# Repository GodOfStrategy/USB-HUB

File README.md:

# USB-HUB
USB-C PD USB 3.0 Hub

A compact USB 3.0 hub based on the TUSB8041 hub controller with USB-C Power Delivery, SD/microSD support, and per-port power protection.
I made this porject to make use of the empty USB-C 3.0 port on my laptop, and since my laptop does not have a SD reader, this hub would be useful.
Features
2× USB 3.0 Type-A ports
SD card reader
microSD card reader
USB-C upstream connection
USB Power Delivery (UPD350A)
USB-C orientation detection and lane switching
Per-port overcurrent protection
USB 3.0 SuperSpeed (5 Gbps)
# Architecture:
USB-C
│
UPD350A (PD Controller)
│
HD3SS3212 (USB-C Lane Mux)
│
TUSB8041 (USB 3.0 Hub)
├── USB 3.0 Port #1
├── USB 3.0 Port #2
├── GL823K SD Reader
└── GL823K microSD Reader

# Power System:
USB-C PD input (5–20V)
Buck converter → 5V rail
Buck converter → 3.3V rail
Buck converter → 1.8V rail
LDO → 1.1V rail (TUSB8041 core)
Protection
TPS2553 on each downstream USB port
900 mA current limit per port
Overcurrent fault reporting to TUSB8041

# Key Components:
Component	PurposeTUSB8041	USB 3.0 Hub Controller
UPD350A	USB-C PD & Orientation Detection
HD3SS3212	SuperSpeed Lane Multiplexer
TPS2553	Port Power Protection
GL823K	USB-to-SD Bridge

# Design Notes:
USB 3.0 differential pairs routed at 90 Ω differential impedance.
HD3SS3212 SEL pin driven by UPD350A orientation output.
TUSB8041 configured for individual port power control.
External 24 MHz crystal used for hub clock generation.

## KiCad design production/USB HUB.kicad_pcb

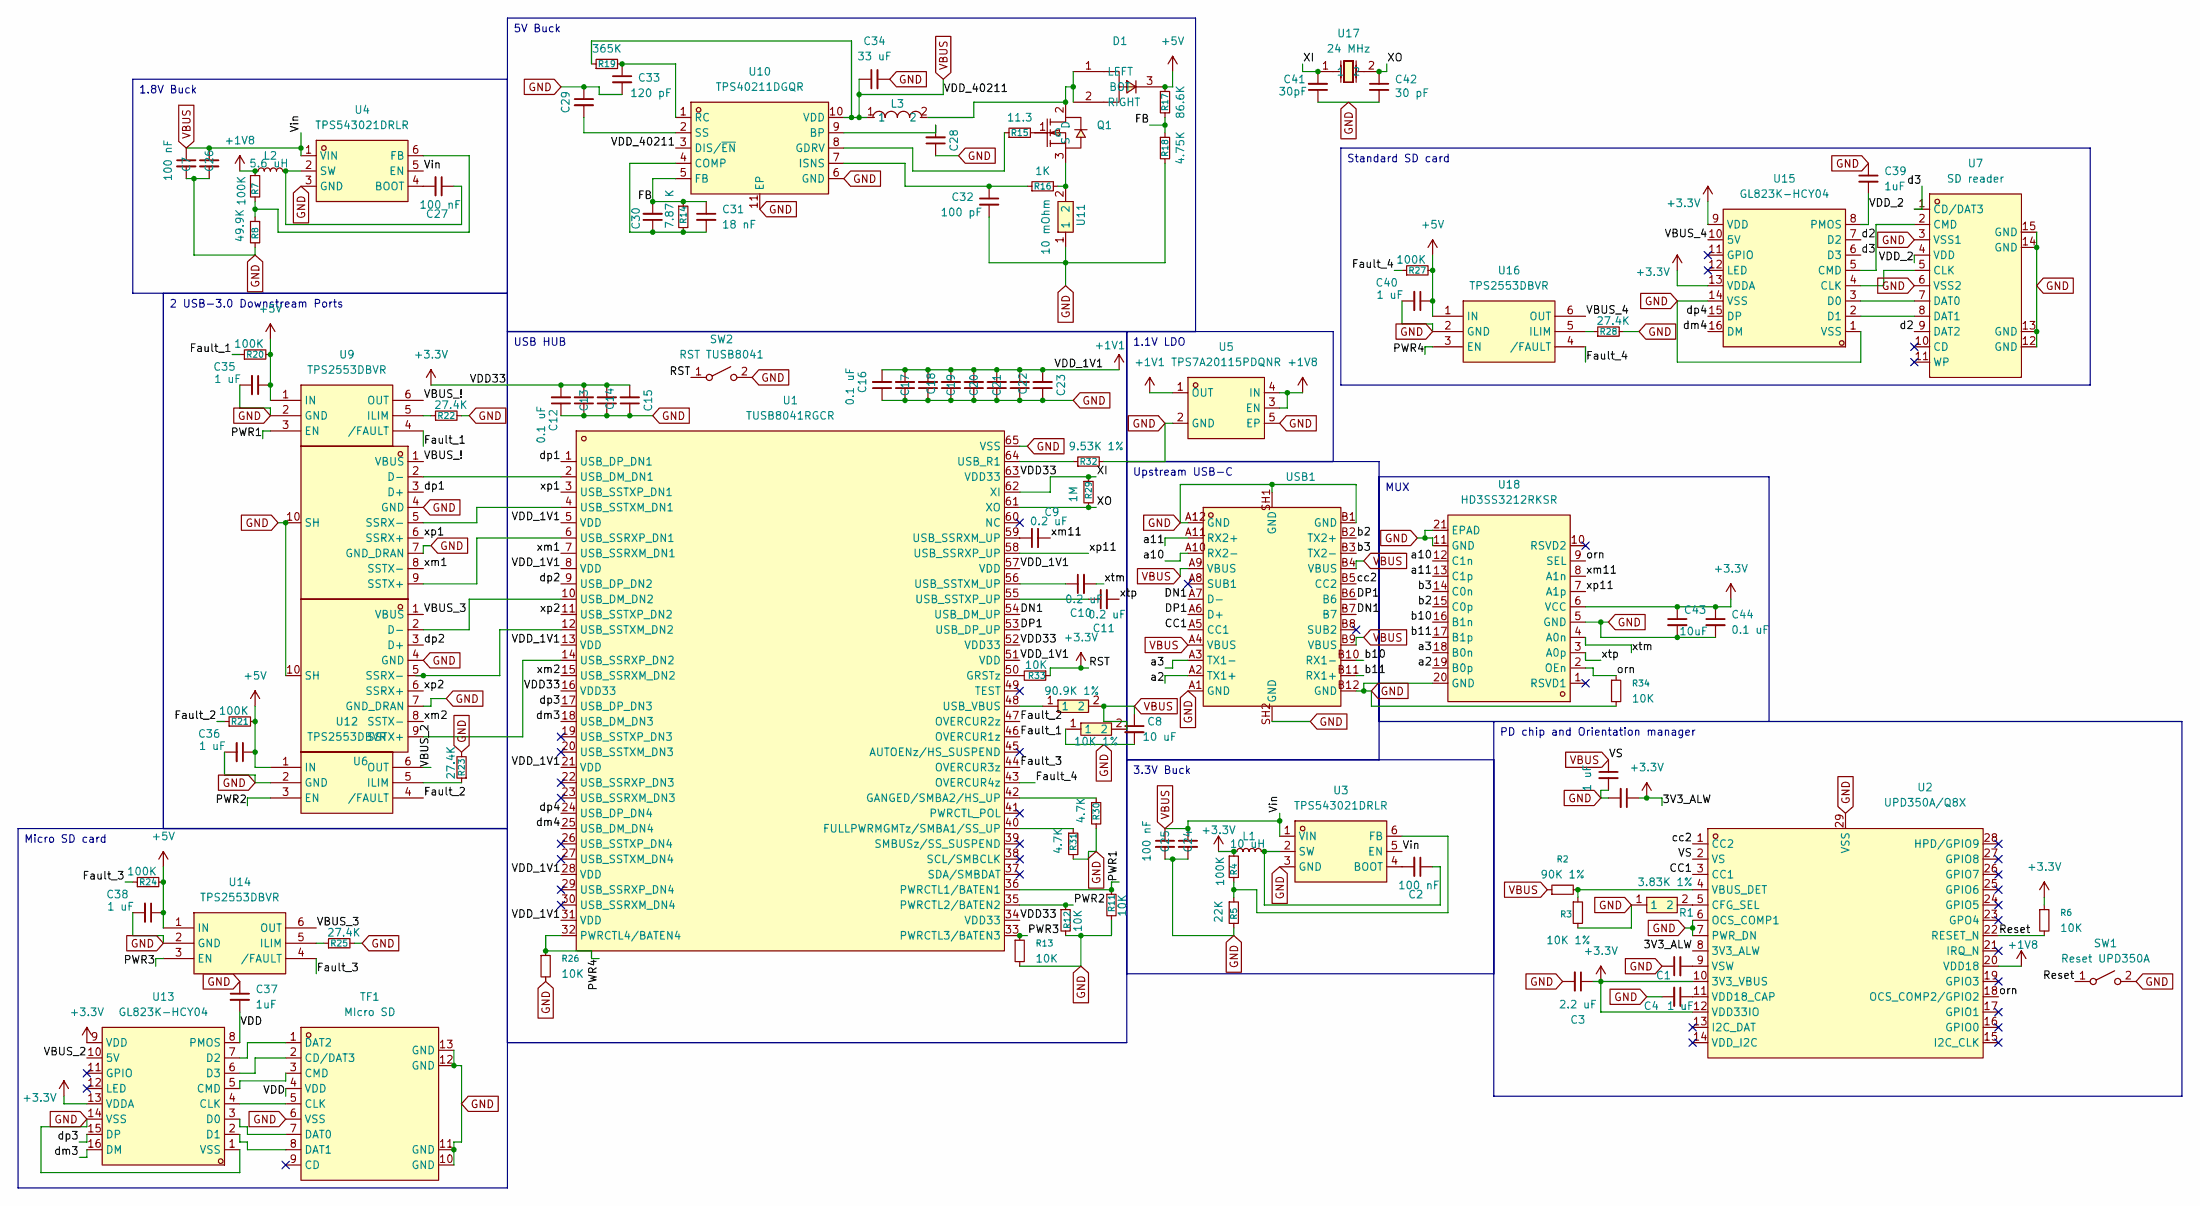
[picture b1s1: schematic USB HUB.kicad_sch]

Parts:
C1, C4, C6, C28, C35, C36, C38, C40: 1 uF; C_0603_1608Metric
C2, C7, C25, C27: 100 nF; C_0805_2012Metric
C3, C5: 2.2 uF; C_0402_1005Metric
C8, C24, C26: 10 uF; C_0603_1608Metric
C9, C10, C11: 0.2 uF; C_0603_1608Metric
C12, C13, C14, C15, C16, C17, C18, C19, C20, C21, C22, C23: 0.1 uF; C_0402_1005Metric
C29: 63 nF; C_1206_3216Metric
C30: 390 pF; C_0402_1005Metric
C31: 18 nF; C_0805_2012Metric
C32: 100 pF; C_0402_1005Metric
C33: 120 pF; C_0402_1005Metric
C34: 33 uF; C_0805_2012Metric
C37, C39: 1uF; C_0603_1608Metric
C41: 30pF; C_0402_1005Metric
C42: 30 pF; C_0402_1005Metric
C43: 10uF; C_0603_1608Metric
C44: 0.1 uF; C_0805_2012Metric
D1: PDS760-13; POWERDI-5_L5.4-W4.0-LS6.5-RD; MPN PDS760-13; LCSC Part C96113
L1: 10 uH; IND-SMD_L6.7-W6.7_CDRH6D26HPNP-4R7PC
L2: 5.6 uH; IND-SMD_L5.2-W5.2_MCW-0530
L3: HMS0530-100M; IND-SMD_HMS0530-4R7M; MPN HMS0530-100M; LCSC Part C18734447
Q1: CSD18534KCS_C2867071; TO-220AB-3_L10.4-W4.6-P2.54-L; MPN CSD18534KCS; LCSC Part C2867071
R1: 3.83K 1%; R0805; MPN FRC0805F3831TS; LCSC Part C2933428
R2: 90K 1%; R_1206_3216Metric
R3: 10K 1%; R_0402_1005Metric
R4, R7, R20, R21, R24, R27: 100K; R_0402_1005Metric
R5: 22K; R_0603_1608Metric
R6, R11, R12, R13, R26, R33, R34: 10K; R_0402_1005Metric
R8: 49.9K; R_0201_0603Metric
R9: 90.9K 1%; R0402; MPN RC0402FR-0790K9L; LCSC Part C163452
R10: 10K 1%; R0402; MPN RC0402FR-0710KL; LCSC Part C60490
R14: 7.87 K; R_0402_1005Metric
R15: 11.3; R_0402_1005Metric
R16: 1K; R_0402_1005Metric
R17: 86.6K; R_0603_1608Metric
R18: 4.75K; R_0603_1608Metric
R19: 365K; R_0603_1608Metric
R22, R23, R25, R28: 27.4K; R_0603_1608Metric
R29: 1M; R_0603_1608Metric
R30, R31: 4.7K; R_0603_1608Metric
R32: 9.53K 1%; R_0603_1608Metric
SW1: Reset UPD350A; SW-SMD_L3.9-W3.0-P4.45
SW2: RST TUSB8041; SW-SMD_L3.9-W3.0-P4.45
TF1: MIcro SD; TF-SMD_TF-CARD-H1.8; MPN TF-CARD H1.8; LCSC Part C7529389
U1: TUSB8041RGCR; QFN-64_L9.0-W9.0-P0.50-BL-EP6.0; MPN TUSB8041RGCR; LCSC Part C486066
U2: UPD350A/Q8X; VQFN-28_L4.0-W4.0-P0.40-BL-EP2.6; MPN UPD350A/Q8X; LCSC Part C633318
U3, U4: TPS543021DRLR; SOT-563-6_L1.6-W1.2-P0.5-LS1.6-BL; MPN TPS543021DRLR; LCSC Part C53283878
U5: TPS7A20115PDQNR; X2SON-4_L1.0-W1.0-P0.65-TL-EP; MPN TPS7A20115PDQNR; LCSC Part C45431438
U6, U8: HC-USB3.0-L168-WP; USB-TH_USB3.0-A; MPN HC-USB3.0-L168-WP; LCSC Part C7501850
U7: SD reader; SD-SMD_HX-SD-CARD-11P; MPN HX SD-CARD 11P; LCSC Part C19189040
U9, U12, U14, U16: TPS2553DBVR; SOT-23-6_L2.9-W1.6-P0.95-LS2.8-BR; MPN TPS2553DBVR; LCSC Part C55266
U10: TPS40211DGQR; MSOP-10_L3.0-W3.0-P0.50-LS5.0-BL-EP-1; MPN TPS40211DGQR; LCSC Part C473356
U11: 10 mOhm; R1206; MPN FRM121WFR010TM; LCSC Part C7467248
U13, U15: GL823K-HCY04; SSOP-16_L4.9-W3.9-P0.64-LS6.0-BL; MPN GL823K-HCY04; LCSC Part C284879
U17: 24 MHz; CRYSTAL-SMD_L11.4-W4.7-LS12.7; MPN ABLS2-25.000MHZ-2X-FT; LCSC Part C1985775
U18: HD3SS3212RKSR; TQFN-20_L4.5-W2.5-P0.50-BL-EP3.0; MPN HD3SS3212RKSR; LCSC Part C129320
USB1: CX60-24S-UNIT; USB-TYPE-C_CX60-24S-UNIT; MPN CX60-24S-UNIT; LCSC Part C5338340

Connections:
+1V1: C16.2, C17.2, C18.2, C19.2, C20.2, C21.2, C22.2, C23.2, U1.5 (VDD), U1.8 (VDD), U1.13 (VDD), U1.21 (VDD), U1.28 (VDD), U1.31 (VDD), U1.51 (VDD), U1.57 (VDD), U5.1 (OUT)
+1V8: L2.1, R7.1, U2.20 (VDD18), U5.3 (EN), U5.4 (IN)
+3.3V: C3.1, C5.1, C12.2, C13.2, C14.2, C15.2, C43.1, C44.1, L1.1, R4.1, R6.1, R33.1, SW2.1 (A), U1.16 (VDD33), U1.34 (VDD33), U1.52 (VDD33), U1.63 (VDD33), U2.8 (3V3_ALW), U2.10 (3V3_VBUS), U2.12 (VDD33IO), U13.9 (VDD), U13.13 (VDDA), U15.9 (VDD), U15.13 (VDDA), U18.6 (VCC)
+5V: C35.1, C36.1, C38.1, C40.1, D1.3 (BOT), R17.1, R20.2, R21.2, R24.2, R27.2, U9.1 (IN), U12.1 (IN), U14.1 (IN), U16.1 (IN)
/CC1: U2.3 (CC1), USB1.A5 (CC1)
/DN1: U1.54 (USB_DM_UP), USB1.A7 (D-), USB1.B7
/DP1: U1.53 (USB_DP_UP), USB1.A6 (D+), USB1.B6
/FB: C30.2, C31.1, R14.1, R17.2, R18.1, U10.5 (FB)
/Fault_1: R20.1, U1.46 (OVERCUR1z), U9.4 (/FAULT)
/Fault_2: R21.1, U1.47 (OVERCUR2z), U12.4 (/FAULT)
/Fault_3: R24.1, U1.44 (OVERCUR3z), U14.4 (/FAULT)
/Fault_4: R27.1, U1.43 (OVERCUR4z), U16.4 (/FAULT)
/PWR1: R11.1, U1.36 (PWRCTL1/BATEN1), U9.3 (EN)
/PWR2: R12.1, U1.35 (PWRCTL2/BATEN2), U12.3 (EN)
/PWR3: R13.1, U1.33 (PWRCTL3/BATEN3), U14.3 (EN)
/PWR4: R26.1, U1.32 (PWRCTL4/BATEN4), U16.3 (EN)
/Reset: R6.2, SW1.1 (A), U2.22 (RESET_N)
/VBUS_2: U12.6 (OUT), U13.10 (5V)
/VBUS_3: U6.1 (VBUS), U14.6 (OUT)
/VBUS_4: U15.10 (5V), U16.6 (OUT)
/VBUS_!: U8.1 (VBUS), U9.6 (OUT)
/VDD: C37.2, TF1.4 (VDD), U13.8 (PMOS)
/VDD_2: C39.2, U7.4 (VDD), U15.8 (PMOS)
/XI: C41.2, R29.1, U1.62 (XI), U17.1
/XO: C42.1, R29.2, U1.61 (XO), U17.2
/a2: U18.19 (B0p), USB1.A2 (TX1+)
/a3: U18.18 (B0n), USB1.A3 (TX1-)
/a10: U18.12 (C1n), USB1.A10 (RX2-), USB1.a10
/a11: U18.13 (C1p), USB1.A11 (RX2+), USB1.a11
/b2: U18.15 (C0p), USB1.B2 (TX2+)
/b3: U18.14 (C0n), USB1.B3 (TX2-), USB1.b3
/b10: U18.16 (B1n), USB1.B10 (RX1-)
/b11: U18.17 (B1p), USB1.B11 (RX1+)
/cc2: U2.1 (CC2), USB1.B5 (CC2)
/d2: U7.9 (DAT2), U15.7 (D2)
/d3: U7.1 (CD/DAT3), U15.6 (D3)
/dm3: U1.18 (USB_DM_DN3), U13.16 (DM)
/dm4: U1.25 (USB_DM_DN4), U15.16 (DM)
/dp1: U1.1 (USB_DP_DN1), U8.3 (D+)
/dp2: U1.9 (USB_DP_DN2), U6.3 (D+)
/dp3: U1.17 (USB_DP_DN3), U13.15 (DP)
/dp4: U1.24 (USB_DP_DN4), U15.15 (DP)
/orn: R34.1, U2.18 (OCS_COMP2/GPIO2), U18.2 (OEn), U18.9 (SEL)
/xm1: U1.7 (USB_SSRXM_DN1), U8.8 (SSTX-)
/xm2: U1.15 (USB_SSRXM_DN2), U6.8 (SSTX-)
/xm11: C9.2, U18.8 (A1n)
/xp1: U1.3 (USB_SSTXP_DN1), U8.6 (SSRX+)
/xp2: U1.11 (USB_SSTXP_DN2), U6.6 (SSRX+)
/xp11: U1.58 (USB_SSRXP_UP), U18.7 (A1p)
/xtm: C10.2, U18.4 (A0n)
/xtp: C11.2, U18.3 (A0p)
GND: C1.1, C3.2, C4.2, C5.2, C6.2, C7.2, C8.2, C12.1, C13.1, C14.1, C15.1, C16.1, C17.1, C18.1, C19.1, C20.1, C21.1, C22.1, C23.1, C24.2, C25.2, C26.2, C28.1, C29.1, C32.2, C33.2, C34.2, C35.2, C36.2, C37.1, C38.2, C39.1, C40.2, C41.1, C42.2, C43.2, C44.2, R1.1, R3.2, R5.2, R8.2, R10.1, R11.2, R12.2, R13.2, R18.2, R22.2, R23.2, R25.2, R26.2, R28.2, R30.2, R31.2, R32.2, R34.2, SW1.2 (B), SW2.2 (B), TF1.6 (VSS), TF1.10 (GND), TF1.11 (GND), TF1.12 (GND), TF1.13 (GND), U1.65 (VSS), U2.6 (OCS_COMP1), U2.7 (PWR_DN), U2.29 (VSS), U3.3 (GND), U4.3 (GND), U5.2 (GND), U5.5 (EP), U6.4 (GND), U6.7 (GND_DRAN), U6.10 (SH), U7.3 (VSS1), U7.6 (VSS2), U7.12 (GND), U7.13 (GND), U7.14 (GND), U7.15 (GND), U8.4 (GND), U8.7 (GND_DRAN), U8.10 (SH), U9.2 (GND), U10.6 (GND), U10.11 (EP), U11.1, U12.2 (GND), U13.1 (VSS), U13.14 (VSS), U14.2 (GND), U15.1 (VSS), U15.14 (VSS), U16.2 (GND), U18.5 (GND), U18.11 (GND), U18.20 (GND), U18.21 (EPAD), USB1.A1 (GND), USB1.A12 (GND), USB1.B1 (GND), USB1.B12 (GND), USB1.SH1 (GND), USB1.SH2 (GND)
unnamed: D1.1 (LEFT), D1.2 (RIGHT), L3.2, Q1.2 (D)
unnamed: Q1.1 (G), R15.2
unnamed: Q1.3 (S), R16.2, U11.2
unnamed: TF1.2 (CD/DAT3), U13.6 (D3)
unnamed: TF1.5 (CLK), U13.4 (CLK)
unnamed: TF1.3 (CMD), U13.5 (CMD)
unnamed: TF1.7 (DAT0), U13.3 (D0)
unnamed: TF1.8 (DAT1), U13.2 (D1)
unnamed: TF1.1 (DAT2), U13.7 (D2)
unnamed: R31.1, U1.40 (FULLPWRMGMTz/SMBA1/SS_UP)
unnamed: R30.1, U1.42 (GANGED/SMBA2/HS_UP)
unnamed: R33.2, U1.50 (GRSTz)
unnamed: U1.2 (USB_DM_DN1), U8.2 (D-)
unnamed: U1.10 (USB_DM_DN2), U6.2 (D-)
unnamed: R32.1, U1.64 (USB_R1)
unnamed: C9.1, U1.59 (USB_SSRXM_UP)
unnamed: U1.6 (USB_SSRXP_DN1), U8.9 (SSTX+)
unnamed: U1.14 (USB_SSRXP_DN2), U6.9 (SSTX+)
unnamed: U1.4 (USB_SSTXM_DN1), U8.5 (SSRX-)
unnamed: U1.12 (USB_SSTXM_DN2), U6.5 (SSRX-)
unnamed: C10.1, U1.56 (USB_SSTXM_UP)
unnamed: C11.1, U1.55 (USB_SSTXP_UP)
unnamed: R9.1, U1.48 (USB_VBUS)
unnamed: R1.2, U2.5 (CFG_SEL)
unnamed: R2.2, R3.1, U2.4 (VBUS_DET)
unnamed: C4.1, U2.11 (VDD18_CAP)
unnamed: C1.2, U2.9 (VSW)
unnamed: C2.2, U3.4 (BOOT)
unnamed: R4.2, R5.1, U3.6 (FB)
unnamed: C2.1, L1.2, U3.2 (SW)
unnamed: C27.2, U4.4 (BOOT)
unnamed: R7.2, R8.1, U4.6 (FB)
unnamed: C27.1, L2.2, U4.2 (SW)
unnamed: R22.1, U9.5 (ILIM)
unnamed: C28.2, U10.9 (BP)
unnamed: C30.1, C31.2, R14.2, U10.4 (COMP)
unnamed: R15.1, U10.8 (GDRV)
unnamed: C32.1, R16.1, U10.7 (ISNS)
unnamed: C33.1, R19.2, U10.1 (RC)
unnamed: C29.2, U10.2 (SS)
unnamed: R23.1, U12.5 (ILIM)
unnamed: R25.1, U14.5 (ILIM)
unnamed: U7.5 (CLK), U15.4 (CLK)
unnamed: U7.2 (CMD), U15.5 (CMD)
unnamed: U7.7 (DAT0), U15.3 (D0)
unnamed: U7.8 (DAT1), U15.2 (D1)
unnamed: R28.1, U16.5 (ILIM)
VBUS: C6.1, C7.1, C8.1, C24.1, C25.1, C26.1, C34.1, L3.1, R2.1, R9.2, R10.2, R19.1, U2.2 (VS), U3.1 (VIN), U3.5 (EN), U4.1 (VIN), U4.5 (EN), U10.3 (DIS/~EN), U10.10 (VDD), USB1.A4 (VBUS), USB1.A9 (VBUS), USB1.B4 (VBUS), USB1.B9 (VBUS)

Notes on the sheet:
3.3V Buck
Standard SD card
2 USB-3.0 Downstream Ports
Micro SD card
PD chip and Orientation manager
USB HUB
Upstream USB-C
MUX
1.1V LDO
1.8V Buck
5V Buck

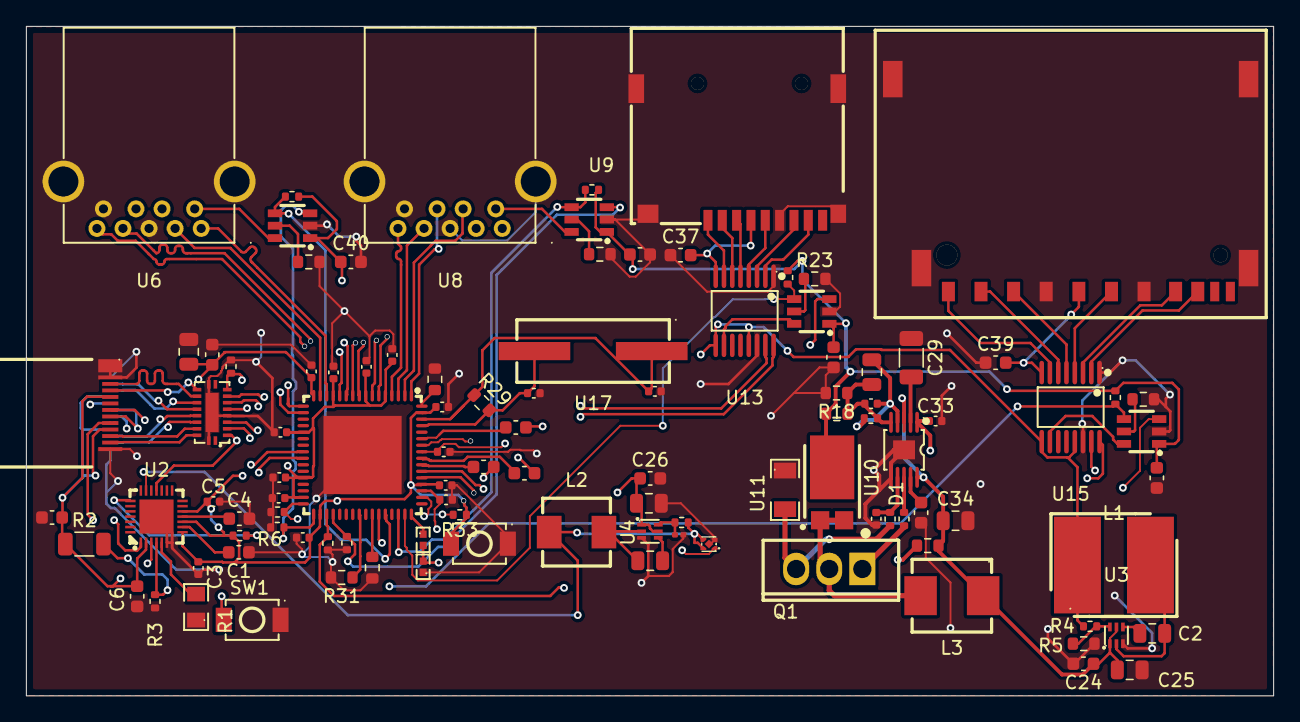
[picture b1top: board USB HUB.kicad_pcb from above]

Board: 4 copper layers, 95.7 x 51.4 mm, 105 parts (0 on the bottom side), 100 nets.
